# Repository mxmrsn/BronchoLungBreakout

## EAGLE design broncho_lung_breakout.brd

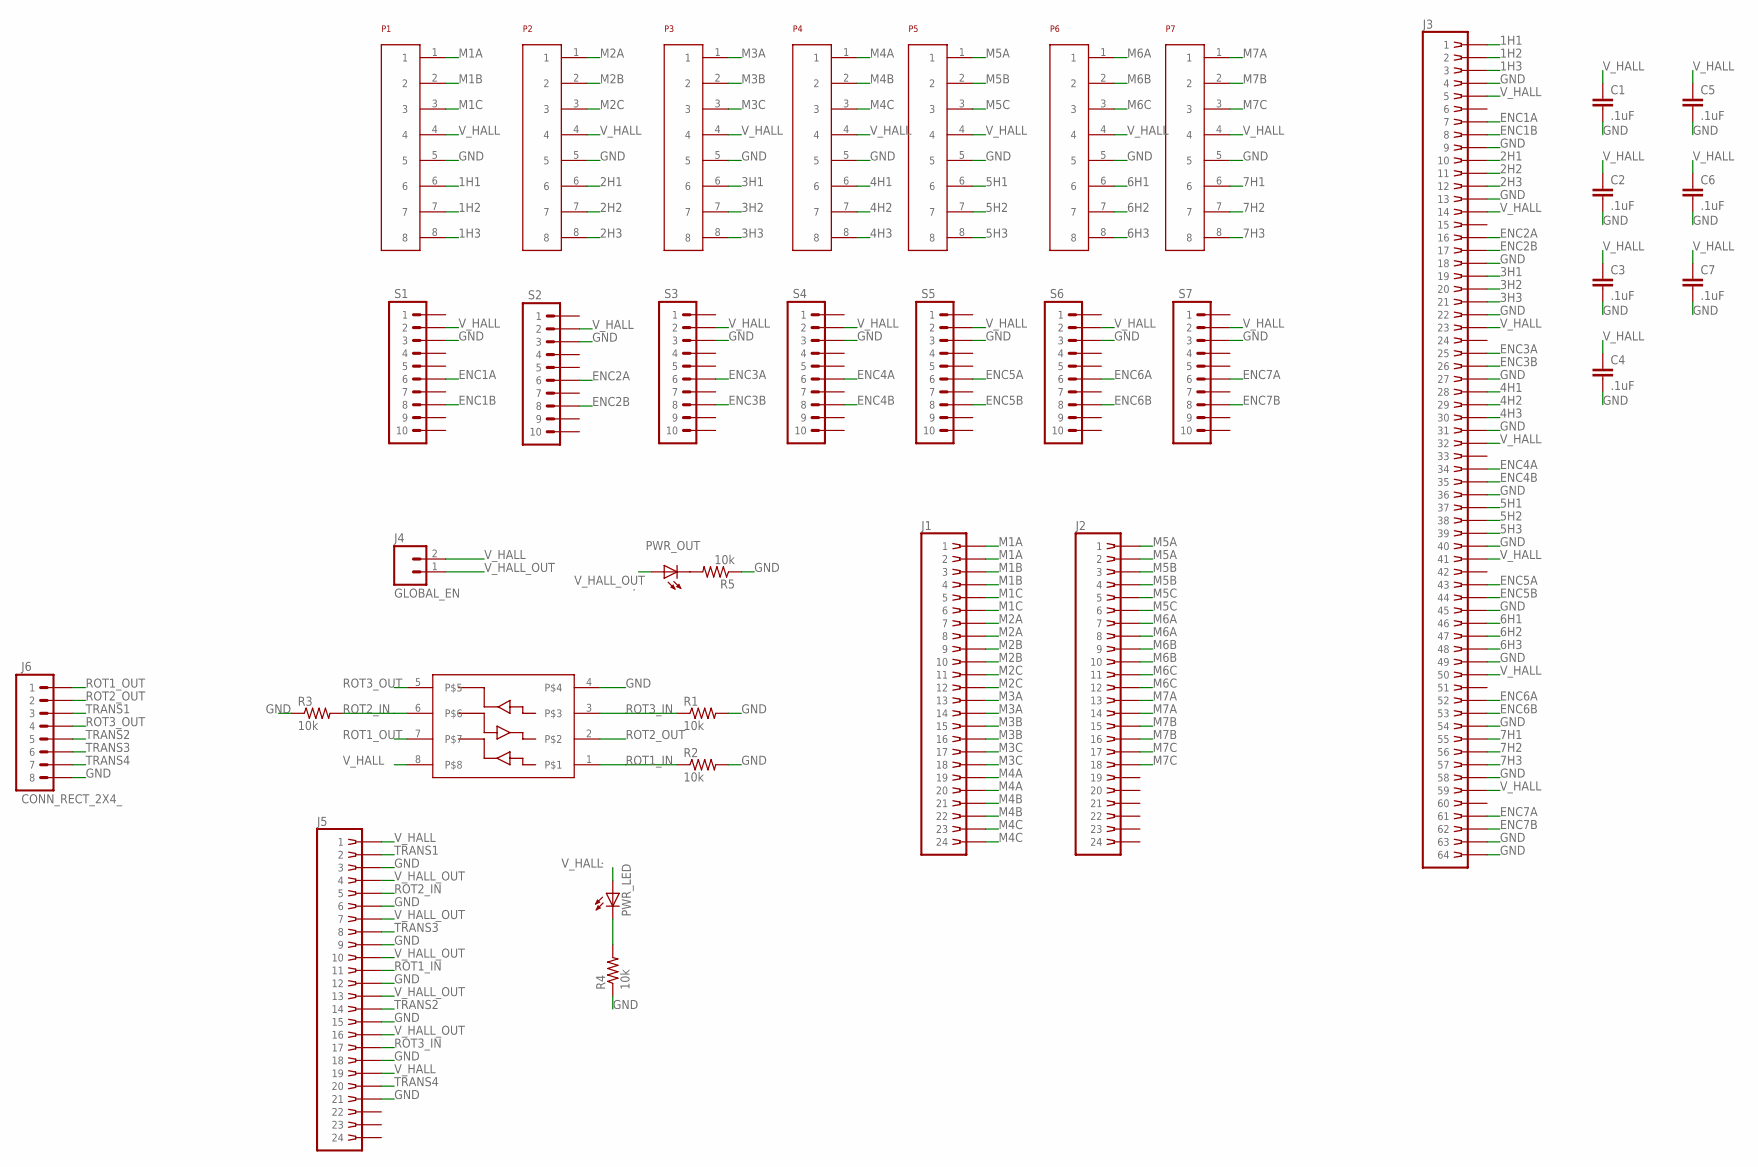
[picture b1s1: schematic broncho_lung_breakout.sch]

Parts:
C1, C2, C3, C4, C5, C6, C7: .1uF; C0603
J1, J2, J5: CONN_RECT_2X12TH; CONN_IDC_24_MALE_TH
J3: CONN_RECT_2X32NOHOLES; CONN_IDC_64_MALE_TH_NOHOLES
J4: GLOBAL_EN; 6410-02
J6: CONN_RECT_2X4_; 2X4
P1, P2, P3, P4, P5, P6, P7: MKS-1650
PWR_LED: .; LED-0805
PWR_OUT: .; LED-0805
R1, R2, R3, R4, R5: 10k; 0603-RES
S1, S2, S3, S4, S5, S6, S7: CONN_RECT_2X5'_VERT; 2X5
U1: INVERTER_3INP; SOP65P405X120-8

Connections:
1H1: J3.P$1 (1), P1.6
1H2: J3.P$2 (2), P1.7
1H3: J3.P$3 (3), P1.8
2H1: J3.P$10 (10), P2.6
2H2: J3.P$11 (11), P2.7
2H3: J3.P$12 (12), P2.8
3H1: J3.P$19 (19), P3.6
3H2: J3.P$20 (20), P3.7
3H3: J3.P$21 (21), P3.8
4H1: J3.P$28 (28), P4.6
4H2: J3.P$29 (29), P4.7
4H3: J3.P$30 (30), P4.8
5H1: J3.P$37 (37), P5.6
5H2: J3.P$38 (38), P5.7
5H3: J3.P$39 (39), P5.8
6H1: J3.P$46 (46), P6.6
6H2: J3.P$47 (47), P6.7
6H3: J3.P$48 (48), P6.8
7H1: J3.P$55 (55), P7.6
7H2: J3.P$56 (56), P7.7
7H3: J3.P$57 (57), P7.8
ENC1A: J3.P$7 (7), S1.6
ENC1B: J3.P$8 (8), S1.8
ENC2A: J3.P$16 (16), S2.6
ENC2B: J3.P$17 (17), S2.8
ENC3A: J3.P$25 (25), S3.6
ENC3B: J3.P$26 (26), S3.8
ENC4A: J3.P$34 (34), S4.6
ENC4B: J3.P$35 (35), S4.8
ENC5A: J3.P$43 (43), S5.6
ENC5B: J3.P$44 (44), S5.8
ENC6A: J3.P$52 (52), S6.6
ENC6B: J3.P$53 (53), S6.8
ENC7A: J3.P$61 (61), S7.6
ENC7B: J3.P$62 (62), S7.8
GND: C1.2, C2.2, C3.2, C4.2, C5.2, C6.2, C7.2, J3.P$4 (4), J3.P$9 (9), J3.P$13 (13), J3.P$18 (18), J3.P$22 (22), J3.P$27 (27), J3.P$31 (31), J3.P$36 (36), J3.P$40 (40), J3.P$45 (45), J3.P$49 (49), J3.P$54 (54), J3.P$58 (58), J3.P$63 (63), J3.P$64 (64), J5.P$3 (3), J5.P$6 (6), J5.P$9 (9), J5.P$12 (12), J5.P$15 (15), J5.P$18 (18), J5.P$21 (21), J6.8, P1.5, P2.5, P3.5, P4.5, P5.5, P6.5, P7.5, R1.2, R2.2, R3.1, R4.1, R5.1, S1.3, S2.3, S3.3, S4.3, S5.3, S6.3, S7.3, U1.4
M1A: J1.P$1 (1), J1.P$2 (2), P1.1
M1B: J1.P$3 (3), J1.P$4 (4), P1.2
M1C: J1.P$5 (5), J1.P$6 (6), P1.3
M2A: J1.P$7 (7), J1.P$8 (8), P2.1
M2B: J1.P$9 (9), J1.P$10 (10), P2.2
M2C: J1.P$11 (11), J1.P$12 (12), P2.3
M3A: J1.P$13 (13), J1.P$14 (14), P3.1
M3B: J1.P$15 (15), J1.P$16 (16), P3.2
M3C: J1.P$17 (17), J1.P$18 (18), P3.3
M4A: J1.P$19 (19), J1.P$20 (20), P4.1
M4B: J1.P$21 (21), J1.P$22 (22), P4.2
M4C: J1.P$23 (23), J1.P$24 (24), P4.3
M5A: J2.P$1 (1), J2.P$2 (2), P5.1
M5B: J2.P$3 (3), J2.P$4 (4), P5.2
M5C: J2.P$5 (5), J2.P$6 (6), P5.3
M6A: J2.P$7 (7), J2.P$8 (8), P6.1
M6B: J2.P$9 (9), J2.P$10 (10), P6.2
M6C: J2.P$11 (11), J2.P$12 (12), P6.3
M7A: J2.P$13 (13), J2.P$14 (14), P7.1
M7B: J2.P$15 (15), J2.P$16 (16), P7.2
M7C: J2.P$17 (17), J2.P$18 (18), P7.3
unnamed: PWR_OUT.C, R5.2
unnamed: PWR_LED.C, R4.2
ROT1_IN: J5.P$11 (11), R2.1, U1.1
ROT1_OUT: J6.1, U1.7
ROT2_IN: J5.P$5 (5), R3.2, U1.6
ROT2_OUT: J6.2, U1.2
ROT3_IN: J5.P$17 (17), R1.1, U1.3
ROT3_OUT: J6.4, U1.5
TRANS1: J5.P$2 (2), J6.3
TRANS2: J5.P$14 (14), J6.5
TRANS3: J5.P$8 (8), J6.6
TRANS4: J5.P$20 (20), J6.7
V_HALL: C1.1, C2.1, C3.1, C4.1, C5.1, C6.1, C7.1, J3.P$5 (5), J3.P$14 (14), J3.P$23 (23), J3.P$32 (32), J3.P$41 (41), J3.P$50 (50), J3.P$59 (59), J4.2, J5.P$1 (1), J5.P$19 (19), P1.4, P2.4, P3.4, P4.4, P5.4, P6.4, P7.4, PWR_LED.A, S1.2, S2.2, S3.2, S4.2, S5.2, S6.2, S7.2, U1.8
V_HALL_OUT: J4.1, J5.P$4 (4), J5.P$7 (7), J5.P$10 (10), J5.P$13 (13), J5.P$16 (16), PWR_OUT.A

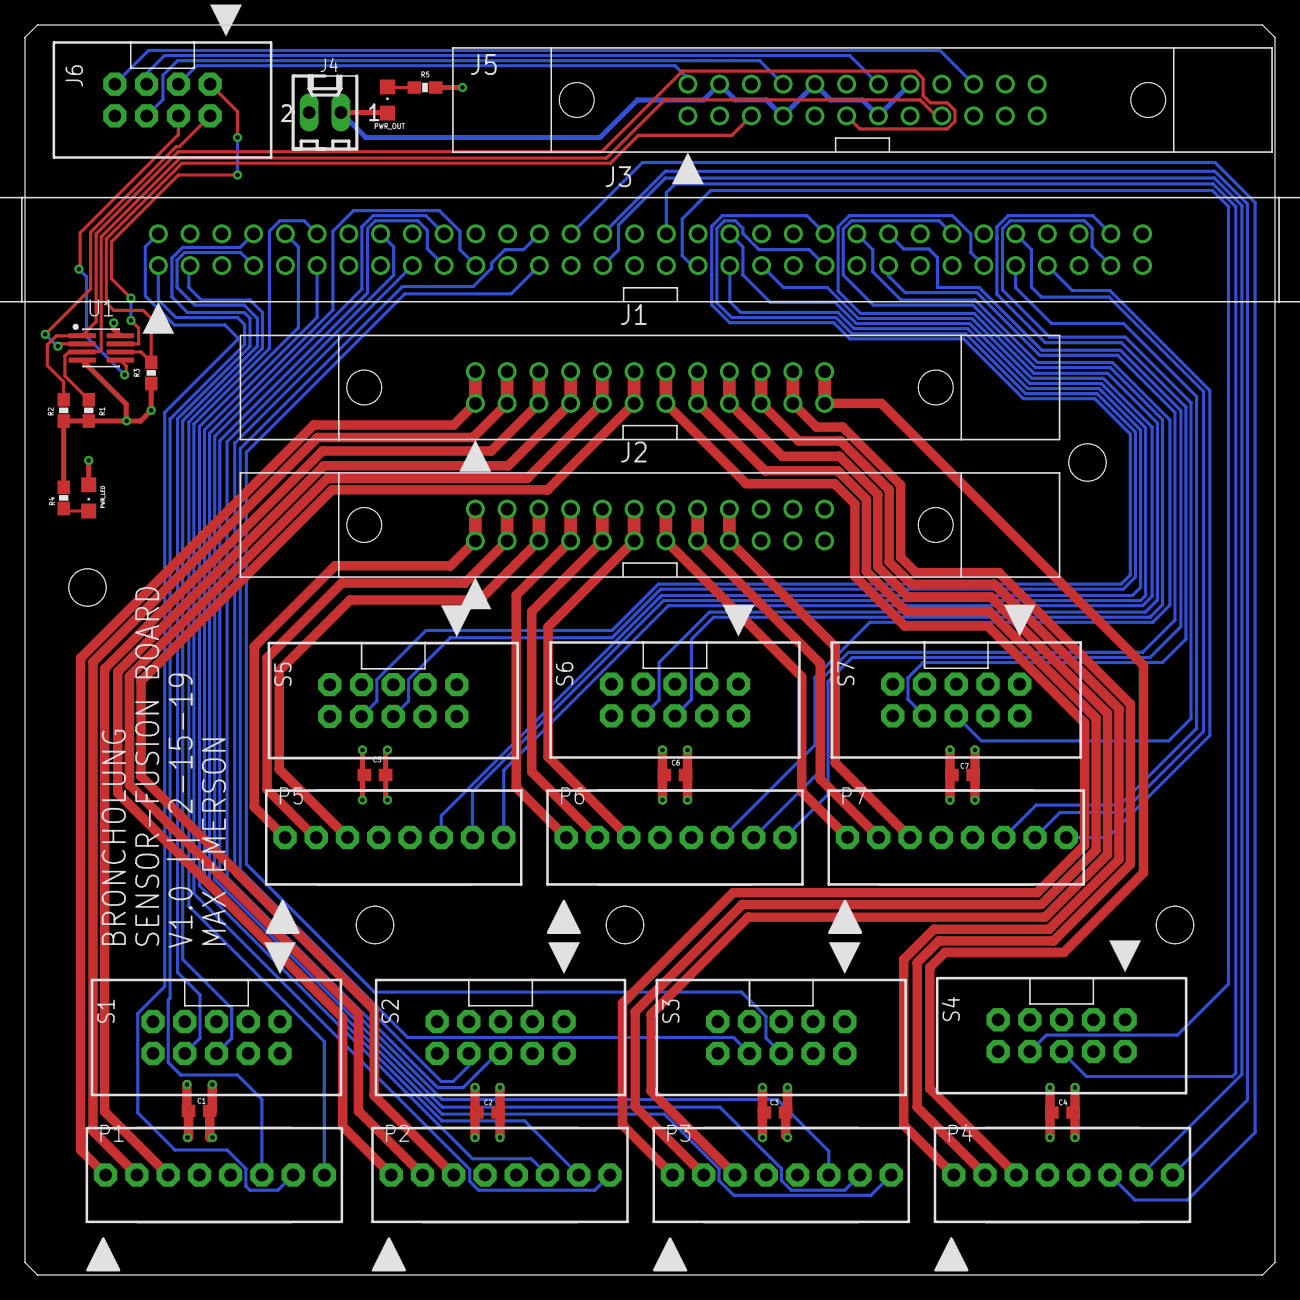
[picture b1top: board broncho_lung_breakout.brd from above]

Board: 4 copper layers, 100.0 x 100.0 mm, 35 parts (0 on the bottom side), 71 nets.

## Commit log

2020-02-14 Cleanup
2020-12-16 Created using Colaboratory
